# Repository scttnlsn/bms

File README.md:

# BMS

Integrated battery management system for 4-series li-ion packs (based on the [BQ76920](http://www.ti.com/product/BQ76920) from Texas Instruments).

* programmable over/under voltage protection for each cell
* programmable short-circuit detection
* auto cell balancing
* cell voltage monitoring
* coulomb counting for accurate state-of-charge tracking
* status available over BLE

## Hardware

Full schematic and PCB layout available in the `hardware` directory.

* [TI BQ76920](http://www.ti.com/product/BQ76920) analog front-end
* [Nordic nRF51822](https://www.nordicsemi.com/eng/Products/Bluetooth-low-energy/nRF51822) ARM Cortex-M host controller
* FETs for enabling or disabling charge/discharge
* shunt resistor for current measurement

## Firmware

The host controller firmware is based on the [Zephyr RTOS](https://www.zephyrproject.org).  It communicates with the BQ76920 via I2C and handles various error states that may occur in the BQ76920.  It also exposes a BLE peripheral for wireless monitoring.

### Build

Requirements:

* [GNU ARM Embedded Toolchain](https://developer.arm.com/open-source/gnu-toolchain/gnu-rm)
* [OpenOCD](http://openocd.org)
* [Zephyr RTOS](https://www.zephyrproject.org) (included as submodule)
* [elftools](https://github.com/eliben/pyelftools)

Setup:

* `git submodule update --init`
* `./setup.sh`

Compile and flash:

* `make`
* `make flash`

### Configuration

There are various configuration options which can be specified via Kconfig.  Run `make menuconfig` to browse the available options and override any of the default values.

* `CONFIG_BMS_BOOT_DEVICE` (default: `GPIO_0`)
* `CONFIG_BMS_BOOT_PIN` (default: `21`)
* `CONFIG_BMS_ALERT_DEVICE` (default: `GPIO_0`)
* `CONFIG_BMS_ALERT_PIN` (default: `22`)
* `CONFIG_BMS_BLINK_DEVICE` (default: `GPIO_0`)
* `CONFIG_BMS_BLINK_PIN` (default: `18`)
* `CONFIG_BMS_OVP_ENABLE` (default: `3550` mV)
* `CONFIG_BMS_OVP_DISABLE` (default: `3350` mV)
* `CONFIG_BMS_UVP_ENABLE` (default: `3000` mV)
* `CONFIG_BMS_UVP_DISABLE` (default: `3100` mV)
* `CONFIG_BMS_SCD_DELAY` (default: `10000` ms)
* `CONFIG_BMS_OCD_DELAY` (default: `10000` ms)

## BLE Protocol

The BMS implements a Bluetooth Low Energy peripheral for monitoring cell voltages, current draw and state-of-charge.  All status data is part of a single characteristic.

Peripheral UUID: `8D9D7800-5B61-412A-AB71-5C7E0E559086`

Characteristic UUID: `8D9D7801-5B61-412A-AB71-5C7E0E559086`

Value structure (MSB to LSB):

* status [1 byte]
* cell 1 (mV) [2 bytes]
* cell 2 (mV) [2 bytes]
* cell 3 (mV) [2 bytes]
* cell 4 (mV) [2 bytes]
* current (mA) [2 bytes signed]
* charge used (mAs) [4 bytes signed]
* state of charge (percent) [1 byte]

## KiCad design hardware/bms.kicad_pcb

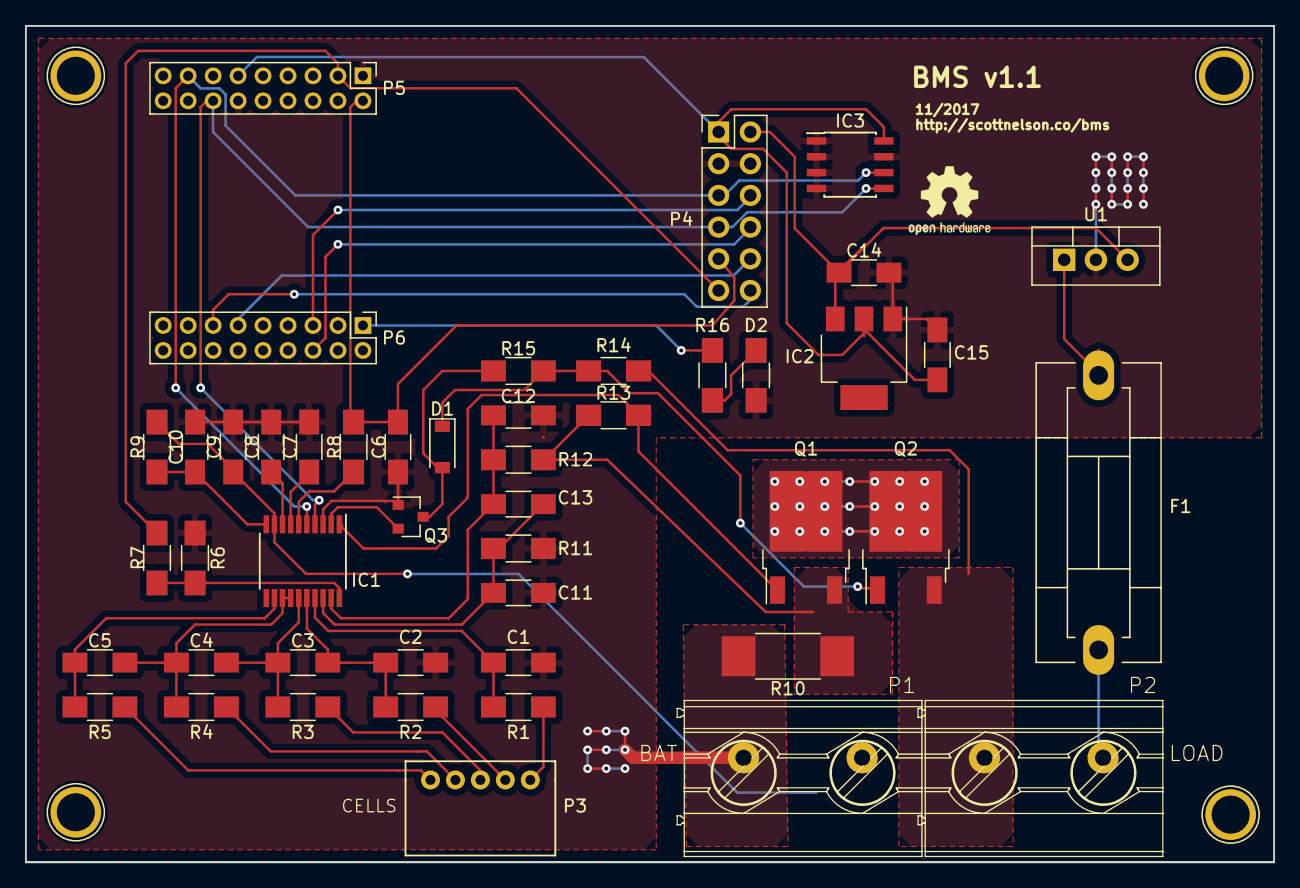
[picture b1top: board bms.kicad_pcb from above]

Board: 2 copper layers, 100.0 x 67.0 mm, 47 parts (0 on the bottom side), 39 nets.

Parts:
C1, C2, C3, C4, C5, C6, C11, C12, C13, C14: 100n; C_1206_HandSoldering
C7, C9: 1u; C_1206_HandSoldering
C8: 4.7u; C_1206_HandSoldering
C10, C15: 10u; C_1206_HandSoldering
D1: 1N4148; D_SOD-123
D2: LED; R_1206_HandSoldering
F1: 200mA; Fuseholder5x20_horiz_SemiClosed_Casing10x25mm
IC1: BQ76920; TSSOP-20_4.4x6.5mm_Pitch0.65mm
IC2: LD1117S33TR_SOT223; SOT-223
IC3: 24LC256; SOIC-8_3.9x4.9mm_Pitch1.27mm
P1: BAT; MKDS_5-2-952
P2: LOAD; MKDS_5-2-952
P3: CONN_01X05; Molex_89401-0510
P4: CONN_02X06; Pin_Header_Straight_2x06_Pitch2.54mm
P5, P6: CONN_02X09; Pin_Header_Straight_2x09_Pitch2.00mm
Q1, Q2: NMOS; TO-252-2
Q3: PMOS; SOT-23
R1, R2, R3, R4, R5: 47R; R_1206_HandSoldering
R6, R13, R14, R15: 1M; R_1206_HandSoldering
R7, R8, R11, R12: 1K; R_1206_HandSoldering
R9: 100R; R_1206_HandSoldering
R10: 5m; R_2512_HandSoldering
R16: 330; R_1206_HandSoldering
U1: TSR 0.5-2450; TO-220-3_Vertical

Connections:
+3V3: C15.1, IC2.2, IC3.8, P4.1, P5.11
+5V: C14.1, IC2.3, P4.2, U1.3
/ALERT: P4.11, P5.3, R7.1
/B1: P3.5, R1.2
/B2: P3.4, R2.2
/B3: P3.3, R3.2
/B4: P3.2, R4.2
/B5: P3.1, R5.2
/BAT+: C9.1, F1.1, IC1.9, P1.2, P2.2, R9.1
/BOOT: C6.1, P4.9, P5.2, R8.1
/CHG: IC1.2, Q3.2
/DSG: IC1.1, Q1.1, R13.2
/LED: P6.1, R16.1
/PACK-: P2.1, Q2.3, R14.1
/RX: P4.10, P6.11
/SCL: IC1.5, IC3.6, P4.5, P5.15
/SDA: IC1.4, IC3.5, P4.7, P5.14
/SRN: C12.2, C13.1, IC1.19, R12.1
/SRP: C11.2, C13.2, IC1.18, R11.1
/SWCLK: P4.8, P6.6
/SWDIO: P4.6, P6.5
/TX: P4.12, P6.13
GND: C1.2, C2.2, C6.2, C7.2, C8.2, C9.2, C10.2, C11.1, C12.1, C14.2, C15.2, D2.1, IC1.3, IC2.1, IC3.1, IC3.2, IC3.3, IC3.4, IC3.7, P1.1, P4.3, P4.4, P5.1, P5.12, Q3.1, R6.1, R10.2, R11.2, U1.2
unnamed: C1.1, IC1.17, R1.1
unnamed: C2.1, C3.2, IC1.16, R2.1
unnamed: C3.1, C4.2, IC1.15, R3.1
unnamed: C4.1, C5.2, IC1.13, IC1.14, R4.1
unnamed: C5.1, IC1.12, R5.1
unnamed: C7.1, IC1.7
unnamed: C8.1, IC1.8
unnamed: C10.1, IC1.10, R9.2
unnamed: D1.1, Q2.1, R14.2, R15.2
unnamed: D1.2, Q3.3, R15.1
unnamed: D2.2, R16.2
unnamed: F1.2, U1.1
unnamed: IC1.6, R8.2
unnamed: IC1.20, R6.2, R7.2
unnamed: Q1.2, Q2.2
unnamed: Q1.3, R10.1, R12.2, R13.1

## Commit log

2017-07-20 Include Zephyr as submodule
2017-07-21 Added additional bq769x0 config
2017-07-21 Added cell voltage logging
2017-07-28 Added alert interrupt handling
2017-07-29 Added basic BLE peripheral for monitoring cell voltages and pack current
2017-07-31 Enable pull down on alert pin
    There's a pull down on the board but was seeing OVRD_ALERT when sending alert signal over ~10" wire
2017-07-31 Perform continuous current monitoring
2017-07-31 Extract device names and pin numbers into Kconfig options
2017-07-31 Disable OVP/UVP when voltages have recovered sufficiently
2017-08-01 Recover from SCD and OCD errors after delay
2017-08-02 Make blinker configurable
2017-08-02 Send charge with BLE notification data
2017-08-02 Calculate SOC based on cumulative charge and battery capacity
2017-08-02 Improved capacity/charge handling
2017-08-07 Custom BLE UUID and docs
2017-08-14 Ugrade Zephyr to the latest master version
2017-08-28 Steady LED when there's a fault
2017-08-28 Update Zephyr
2017-09-20 Added CRC bytes to all I2C messages
2017-12-09 Added hardware
2017-12-10 Fix regulator grounding issue on PCB
2018-01-24 Upgrade Zephyr, transition to cmake build
2018-01-24 Pack BLE data struct (to be parsed as little endian)
2018-01-24 Added BLE status script
2021-06-16 Include status in BLE packet
2021-06-16 Recover from OCD and SCD faults
